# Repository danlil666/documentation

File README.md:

# danlil666.github.io

Hello there!

This is the starting point of me trying to use GitHub.

The folder `docs` contains my attempt to trying to establish a project website for Prof. Nadya's class.

Hope you are having fun and see y'all there.

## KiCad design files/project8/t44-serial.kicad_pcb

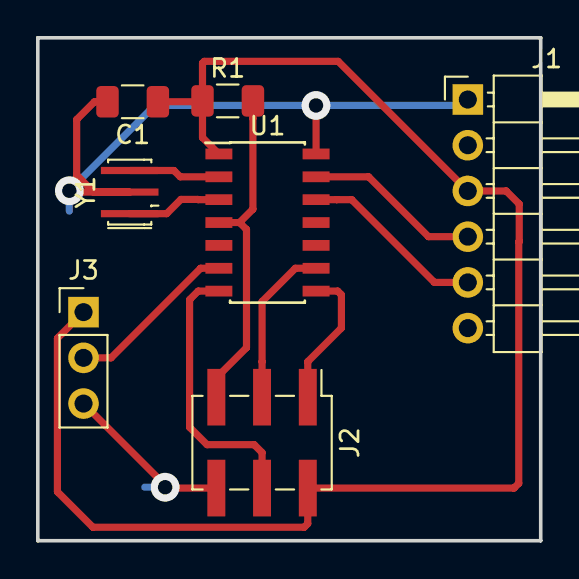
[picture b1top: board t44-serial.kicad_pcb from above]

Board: 2 copper layers, 27.9 x 27.9 mm, 7 parts (0 on the bottom side), 11 nets.

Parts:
C1: 0.1UF; C_1206_3216Metric
J1: Conn_01x06_Male; PinHeader_1x06_P2.54mm_Horizontal
J2: AVR-ISP-6; PinHeader_2x03_P2.54mm_Vertical_SMD
J3: Conn_01x03_Male; PinHeader_1x03_P2.54mm_Vertical
R1: 10K; R_1206_3216Metric
U1: ATtiny44A-SSU; SOIC-14_3.9x8.7mm_P1.27mm
Y1: Resonator; Resonator_SMD_muRata_CSTxExxV-3Pin_3.0x1.1mm_HandSoldering

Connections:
/MISO: J2.1, U1.8
/MOSI: J2.4, U1.7
/RESET: J2.5, R1.2, U1.4
/RX: J1.5, U1.12
/SCK: J2.3, U1.9
/TX: J1.4, U1.13
/read: J3.2, U1.6
GND: C1.2, J1.1, J2.6, J3.3, U1.14, Y1.2
unnamed: U1.2, Y1.3
unnamed: U1.3, Y1.1
VCC: C1.1, J1.3, J2.2, J3.1, R1.1, U1.1

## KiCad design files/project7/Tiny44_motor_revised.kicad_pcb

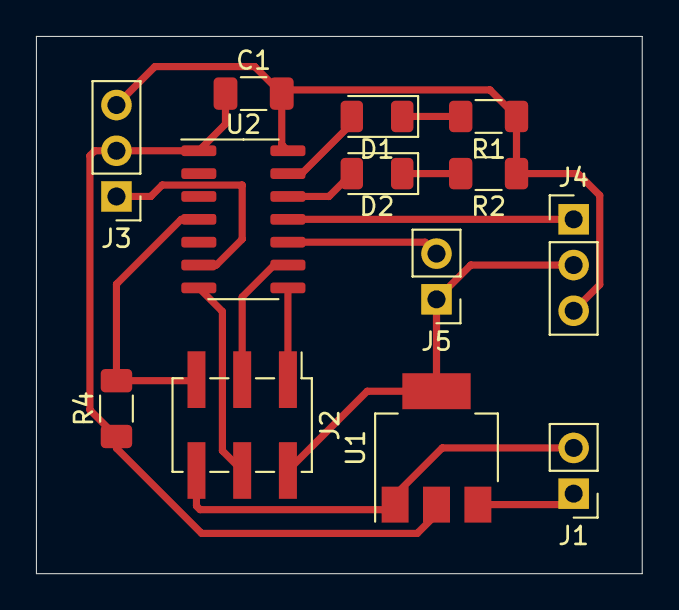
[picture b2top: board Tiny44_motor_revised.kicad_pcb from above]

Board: 2 copper layers, 33.7 x 29.8 mm, 13 parts (0 on the bottom side), 14 nets.

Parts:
C1: 4.7 uF; C_1206_3216Metric_Pad1.33x1.80mm_HandSolder
D1, D2: LED; LED_1206_3216Metric
J1, J5: Conn_01x02_Male; PinHeader_1x02_P2.54mm_Vertical
J2: AVR-ISP-6; PinHeader_2x03_P2.54mm_Vertical_SMD
J3, J4: Conn_01x03_Male; PinHeader_1x03_P2.54mm_Vertical
R1, R2: 1k; R_1206_3216Metric_Pad1.30x1.75mm_HandSolder
R4: 10k; R_1206_3216Metric_Pad1.30x1.75mm_HandSolder
U1: ZLDO1117; SOT-223
U2: ATtiny44A-SSU; SOIC-14_3.9x8.7mm_P1.27mm

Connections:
+9V: J1.1, U1.3
/MISO: J2.1, U2.8
/MOSI: J2.4, U2.7
/Motor1: J3.1, U2.6
/Motor2: J4.1, U2.11
/RESET: J2.5, R4.2, U2.4
/SCK: J2.3, U2.9
/Send: J5.2, U2.10
GND: C1.2, J1.2, J2.6, J3.3, J4.3, R1.1, R2.1, U1.1, U2.14
unnamed: D1.1, R1.2
unnamed: D1.2, U2.13
unnamed: D2.1, R2.2
unnamed: D2.2, U2.12
VCC: C1.1, J2.2, J3.2, J4.2, J5.1, R4.1, U1.2, U1.4, U2.1

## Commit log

2023-03-09 initiate
2024-10-31 updated documentation
2024-10-31 Update Gemfile
2024-10-31 my local changes
2024-10-31 added folder
